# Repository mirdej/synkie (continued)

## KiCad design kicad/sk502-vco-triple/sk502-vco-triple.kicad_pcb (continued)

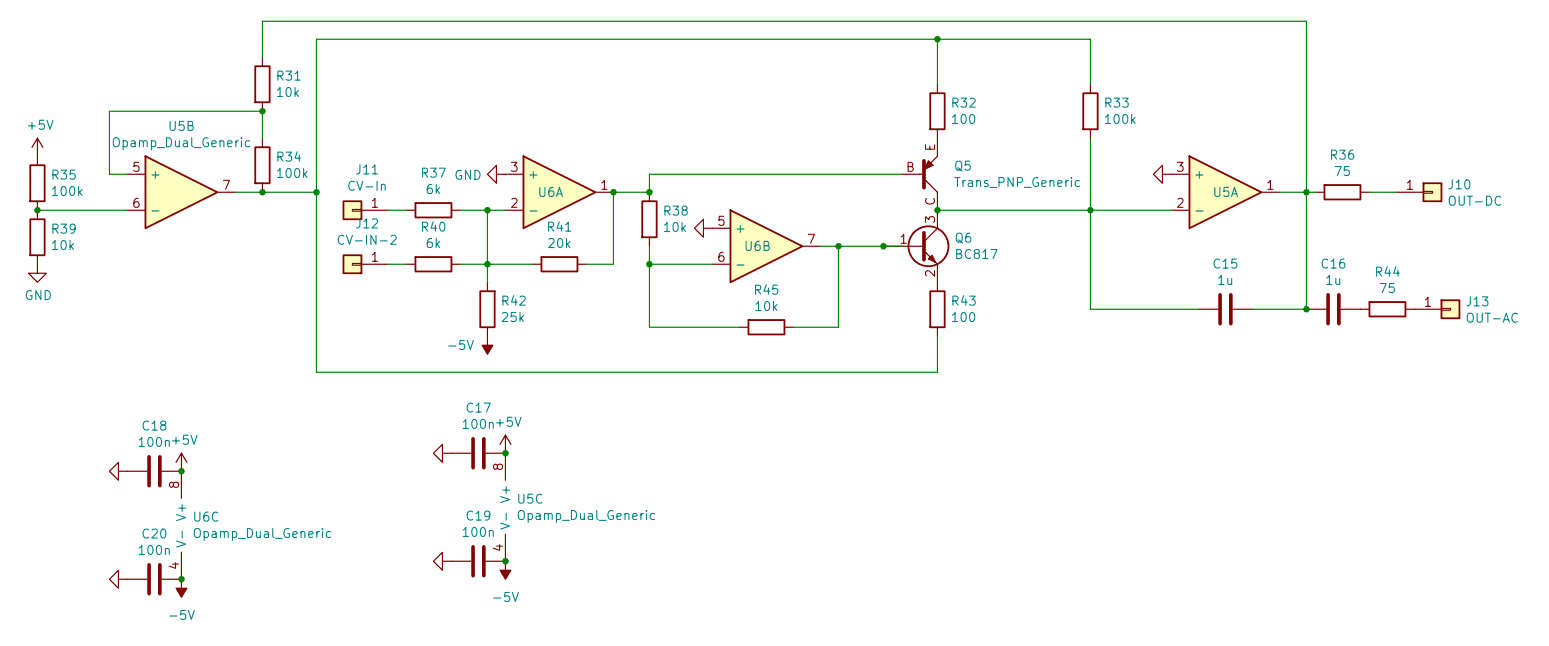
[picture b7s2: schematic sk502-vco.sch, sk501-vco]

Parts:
C3, C4: 1u; C_1206_3216Metric_Pad1.42x1.75mm_HandSolder
C5, C6, C7, C8: 100n; C_0603_1608Metric_Pad1.05x0.95mm_HandSolder
J2: OUT-DC; TestPoint_THTPad_D4.0mm_Drill2.0mm
J3: CV-In; TestPoint_THTPad_D4.0mm_Drill2.0mm
J4: CV-IN-2; TestPoint_THTPad_D4.0mm_Drill2.0mm
J5: OUT-AC; TestPoint_THTPad_D4.0mm_Drill2.0mm
Q1: Trans_PNP_Generic; SOT-23_BEC
Q2: BC817; SOT-23
R1, R8, R9, R15: 10k; R_0805_2012Metric_Pad1.15x1.40mm_HandSolder
R2, R13: 100; R_0805_2012Metric_Pad1.15x1.40mm_HandSolder
R3, R4, R5: 100k; R_0805_2012Metric_Pad1.15x1.40mm_HandSolder
R6, R14: 75; R_0805_2012Metric_Pad1.15x1.40mm_HandSolder
R7, R10: 6k; R_0805_2012Metric_Pad1.15x1.40mm_HandSolder
R11: 20k; R_0805_2012Metric_Pad1.15x1.40mm_HandSolder
R12: 25k; R_0805_2012Metric_Pad1.15x1.40mm_HandSolder
U1, U2: Opamp_Dual_Generic; SOIC-8_3.9x4.9mm_P1.27mm

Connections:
+5V: C5.1, C6.1, R5.1, U1.8 (V+), U2.8 (V+); also elsewhere on the board
-5V: C7.1, C8.1, R12.1, U1.4 (V-), U2.4 (V-); also elsewhere on the board
GND: C5.2, C6.2, C7.2, C8.2, R9.2, U1.3 (+), U2.3 (+), U2.5 (+); also elsewhere on the board
unnamed: C3.1, C4.2, R1.1, R6.2, U1.1
unnamed: C3.2, Q1.C, Q2.3 (C), R3.2, U1.2 (-)
unnamed: C4.1, R14.2
unnamed: J2.1, R6.1
unnamed: J3.1, R7.2
unnamed: J4.1, R10.2
unnamed: J5.1, R14.1
unnamed: Q1.B, R8.1, R11.1, U2.1
unnamed: Q1.E, R2.2
unnamed: Q2.1 (B), R15.1, U2.7
unnamed: Q2.2 (E), R13.1
unnamed: R1.2, R4.1, U1.5 (+)
unnamed: R5.2, R9.1, U1.6 (-)
unnamed: R7.1, R10.1, R11.2, R12.2, U2.2 (-)
unnamed: R2.1, R3.1, R4.2, R13.2, U1.7
unnamed: R8.2, R15.2, U2.6 (-)

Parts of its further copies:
C9, C10, C15, C16: 1u; C_1206_3216Metric_Pad1.42x1.75mm_HandSolder
C11, C12, C13, C14, C17, C18, C19, C20: 100n; C_0603_1608Metric_Pad1.05x0.95mm_HandSolder
J6, J10: OUT-DC; TestPoint_THTPad_D4.0mm_Drill2.0mm
J7, J11: CV-In; TestPoint_THTPad_D4.0mm_Drill2.0mm
J8, J12: CV-IN-2; TestPoint_THTPad_D4.0mm_Drill2.0mm
J9, J13: OUT-AC; TestPoint_THTPad_D4.0mm_Drill2.0mm
Q3, Q5: Trans_PNP_Generic; SOT-23_BEC
Q4, Q6: BC817; SOT-23
R16, R23, R24, R30, R31, R38, R39, R45: 10k; R_0805_2012Metric_Pad1.15x1.40mm_HandSolder
R17, R28, R32, R43: 100; R_0805_2012Metric_Pad1.15x1.40mm_HandSolder
R18, R19, R20, R33, R34, R35: 100k; R_0805_2012Metric_Pad1.15x1.40mm_HandSolder
R21, R29, R36, R44: 75; R_0805_2012Metric_Pad1.15x1.40mm_HandSolder
R22, R25, R37, R40: 6k; R_0805_2012Metric_Pad1.15x1.40mm_HandSolder
R26, R41: 20k; R_0805_2012Metric_Pad1.15x1.40mm_HandSolder
R27, R42: 25k; R_0805_2012Metric_Pad1.15x1.40mm_HandSolder
U3, U4, U5, U6: Opamp_Dual_Generic; SOIC-8_3.9x4.9mm_P1.27mm

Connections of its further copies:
+5V: C11.1, C12.1, C17.1, C18.1, R20.1, R35.1, U3.8 (V+), U4.8 (V+), U5.8 (V+), U6.8 (V+); also elsewhere on the board
-5V: C13.1, C14.1, C19.1, C20.1, R27.1, R42.1, U3.4 (V-), U4.4 (V-), U5.4 (V-), U6.4 (V-); also elsewhere on the board
GND: C11.2, C12.2, C13.2, C14.2, C17.2, C18.2, C19.2, C20.2, R24.2, R39.2, U3.3 (+), U4.3 (+), U4.5 (+), U5.3 (+), U6.3 (+), U6.5 (+); also elsewhere on the board
unnamed: C9.2, Q3.C, Q4.3 (C), R18.2, U3.2 (-)
unnamed: C10.1, R29.2
unnamed: C9.1, C10.2, R16.1, R21.2, U3.1
unnamed: C15.1, C16.2, R31.1, R36.2, U5.1
unnamed: C15.2, Q5.C, Q6.3 (C), R33.2, U5.2 (-)
unnamed: C16.1, R44.2
unnamed: J6.1, R21.1
unnamed: J7.1, R22.2
unnamed: J8.1, R25.2
unnamed: J9.1, R29.1
unnamed: J10.1, R36.1
unnamed: J11.1, R37.2
unnamed: J12.1, R40.2
unnamed: J13.1, R44.1
unnamed: Q3.B, R23.1, R26.1, U4.1
unnamed: Q3.E, R17.2
unnamed: Q4.1 (B), R30.1, U4.7
unnamed: Q4.2 (E), R28.1
unnamed: Q5.B, R38.1, R41.1, U6.1
unnamed: Q5.E, R32.2
unnamed: Q6.1 (B), R45.1, U6.7
unnamed: Q6.2 (E), R43.1
unnamed: R16.2, R19.1, U3.5 (+)
unnamed: R17.1, R18.1, R19.2, R28.2, U3.7
unnamed: R20.2, R24.1, U3.6 (-)
unnamed: R22.1, R25.1, R26.2, R27.2, U4.2 (-)
unnamed: R23.2, R30.2, U4.6 (-)
unnamed: R31.2, R34.1, U5.5 (+)
unnamed: R32.1, R33.1, R34.2, R43.2, U5.7
unnamed: R35.2, R39.1, U5.6 (-)
unnamed: R37.1, R40.1, R41.2, R42.2, U6.2 (-)
unnamed: R38.2, R45.2, U6.6 (-)

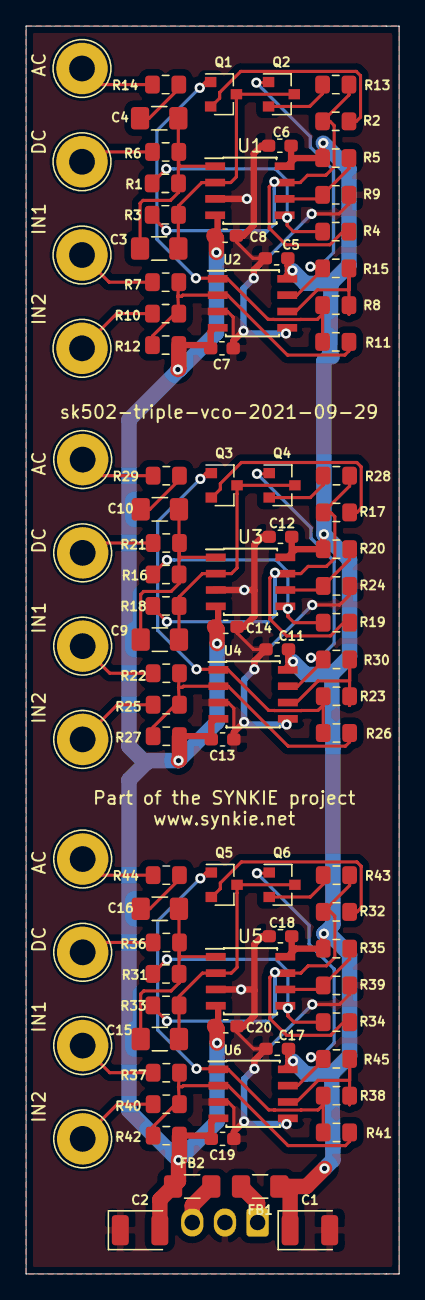
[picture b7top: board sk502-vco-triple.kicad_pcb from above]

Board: 2 copper layers, 29.0 x 97.0 mm, 92 parts (1 on the bottom side), 53 nets.

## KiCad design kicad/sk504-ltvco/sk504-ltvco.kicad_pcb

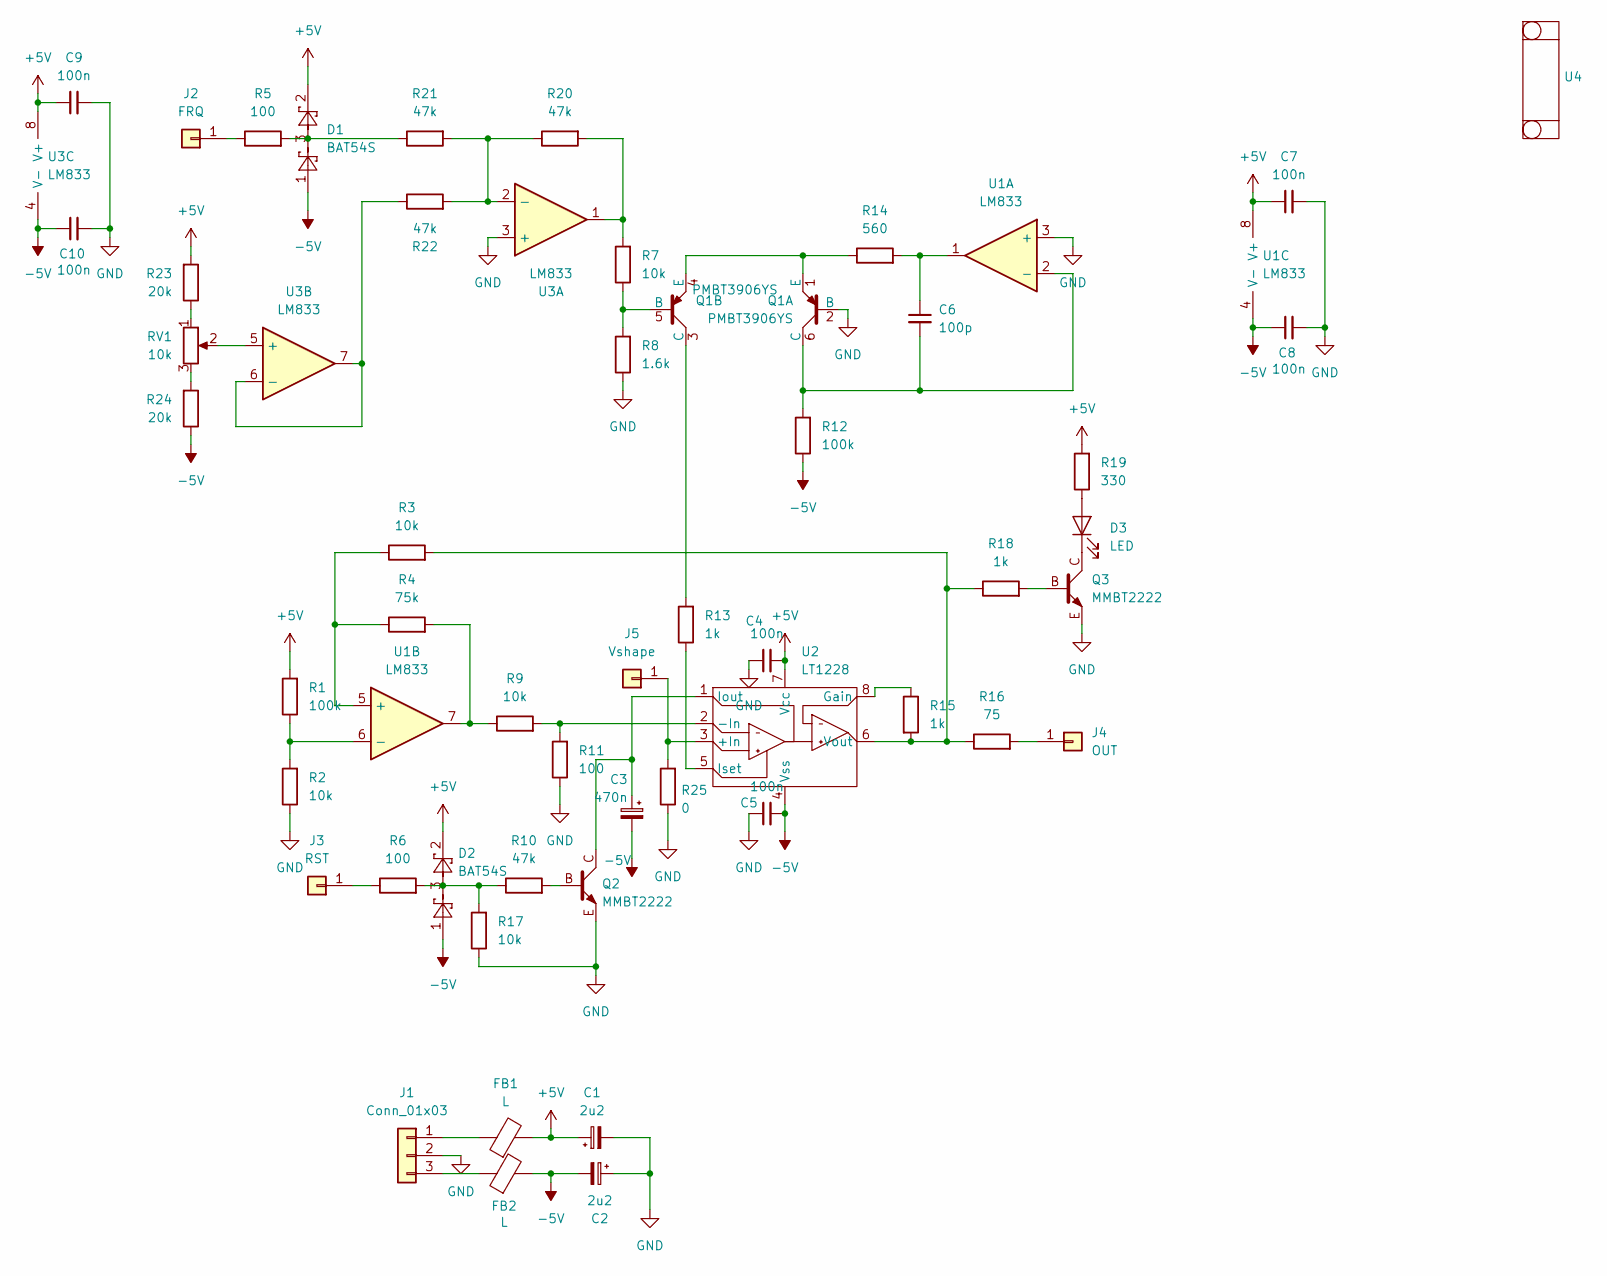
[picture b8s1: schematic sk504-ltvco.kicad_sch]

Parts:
C1, C2: 2u2; C_1206_3216Metric_Pad1.42x1.75mm_HandSolder
C3: 470n; C_1206_3216Metric_Pad1.42x1.75mm_HandSolder
C4, C5, C7, C8, C9, C10: 100n; C_0603_1608Metric_Pad1.05x0.95mm_HandSolder
C6: 100p; C_0603_1608Metric_Pad1.05x0.95mm_HandSolder
D1, D2: BAT54S; SOT-23
D3: LED; LED_0805_2012Metric
FB1, FB2: L; L_0805_2012Metric_Pad1.15x1.40mm_HandSolder
J1: Conn_01x03; Molex_KK-254_AE-6410-03A_1x03_P2.54mm_Vertical_SMD
J2: FRQ; Solderpad-SYNKIEPAD-2mm
J3: RST; Solderpad-SYNKIEPAD-2mm
J4: OUT; Solderpad-SYNKIEPAD-2mm
J5: Vshape; TestPoint_Pad_2.0x2.0mm
Q1: PMBT3906YS; SOT-363_SC-70-6_Handsoldering
Q2, Q3: MMBT2222; SOT-23_BEC
R1, R12: 100k; R_0805_2012Metric_Pad1.15x1.40mm_HandSolder
R2, R3, R7, R9, R17: 10k; R_0805_2012Metric_Pad1.15x1.40mm_HandSolder
R4: 75k; R_0805_2012Metric_Pad1.15x1.40mm_HandSolder
R5, R6, R11: 100; R_0805_2012Metric_Pad1.15x1.40mm_HandSolder
R8: 1.6k; R_0805_2012Metric_Pad1.15x1.40mm_HandSolder
R10, R20, R21, R22: 47k; R_0805_2012Metric_Pad1.15x1.40mm_HandSolder
R13, R15, R18: 1k; R_0805_2012Metric_Pad1.15x1.40mm_HandSolder
R14: 560; R_0805_2012Metric_Pad1.15x1.40mm_HandSolder
R16: 75; R_0805_2012Metric_Pad1.15x1.40mm_HandSolder
R19: 330; R_0805_2012Metric_Pad1.15x1.40mm_HandSolder
R23, R24: 20k; R_0805_2012Metric_Pad1.15x1.40mm_HandSolder
R25: 0; R_0805_2012Metric_Pad1.15x1.40mm_HandSolder
RV1: 10k; Alps_RK097_Frontplate
U1, U3: LM833; SOIC-8_3.9x4.9mm_P1.27mm
U2: LT1228; SOIC-8_3.9x4.9mm_P1.27mm
U4: Frontplate_20mm

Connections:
+5V: C1.1, C4.2, C7.1, C9.1, D1.2, D2.2, FB1.2, R1.2, R19.2, R23.2, U1.8 (V+), U2.7 (Vcc), U3.8 (V+)
-5V: C2.2, C3.2, C5.2, C8.1, C10.1, D1.1, D2.1, FB2.2, R12.1, R24.1, U1.4 (V-), U2.4 (Vss), U3.4 (V-)
GND: C1.2, C2.1, C4.1, C5.1, C7.2, C8.2, C9.2, C10.2, J1.2, Q1.2 (B), Q2.E, Q3.E, R2.1, R8.1, R11.1, R17.1, R25.1, U1.3 (+), U3.3 (+)
unnamed: C6.1, R14.2, U1.1
unnamed: D1.3, R5.2, R21.1
unnamed: D2.3, R6.2, R10.1, R17.2
unnamed: D3.2 (A), R19.1
unnamed: D3.1 (K), Q3.C
unnamed: FB1.1, J1.1
unnamed: FB2.1, J1.3
unnamed: J2.1, R5.1
unnamed: J3.1, R6.1
unnamed: J4.1, R16.2
unnamed: J5.1, R25.2, U2.3 (+In)
unnamed: C6.2, Q1.6 (C), R12.2, U1.2 (-)
unnamed: Q1.1 (E), Q1.4 (E), R14.1
unnamed: Q1.5 (B), R7.1, R8.2
unnamed: Q1.3 (C), R13.2
unnamed: Q2.B, R10.2
unnamed: Q3.B, R18.2
unnamed: R4.2, R9.1, U1.7
unnamed: R7.2, R20.2, U3.1
unnamed: R23.1, RV1.1
unnamed: R24.2, RV1.3
unnamed: R3.1, R4.1, U1.5 (+)
unnamed: R1.1, R2.2, U1.6 (-)
unnamed: R9.2, R11.2, U2.2 (-In)
unnamed: R15.1, U2.8 (Gain)
unnamed: C3.1, Q2.C, U2.1 (Iout)
unnamed: R13.1, U2.5 (Iset)
unnamed: R3.2, R15.2, R16.1, R18.1, U2.6 (Vout)
unnamed: R20.1, R21.2, R22.2, U3.2 (-)
unnamed: RV1.2, U3.5 (+)
unnamed: R22.1, U3.6 (-), U3.7

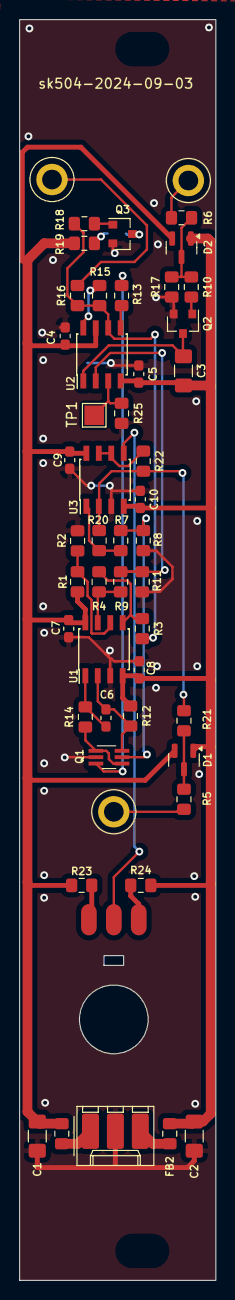
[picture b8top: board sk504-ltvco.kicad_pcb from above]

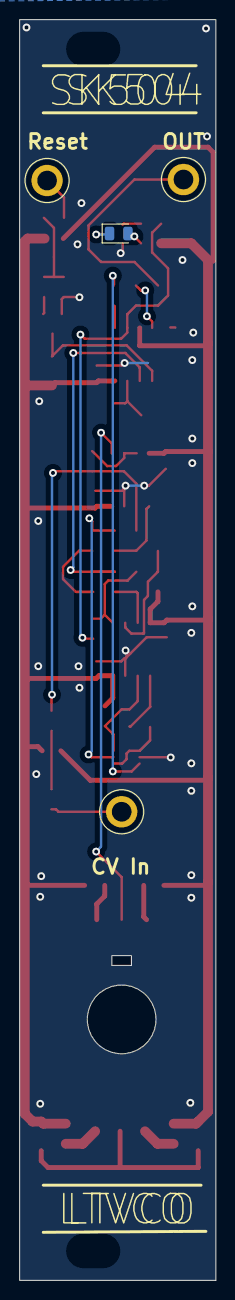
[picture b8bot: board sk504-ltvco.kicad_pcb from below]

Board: 2 copper layers, 20.0 x 128.5 mm, 53 parts (3 on the bottom side), 34 nets.
